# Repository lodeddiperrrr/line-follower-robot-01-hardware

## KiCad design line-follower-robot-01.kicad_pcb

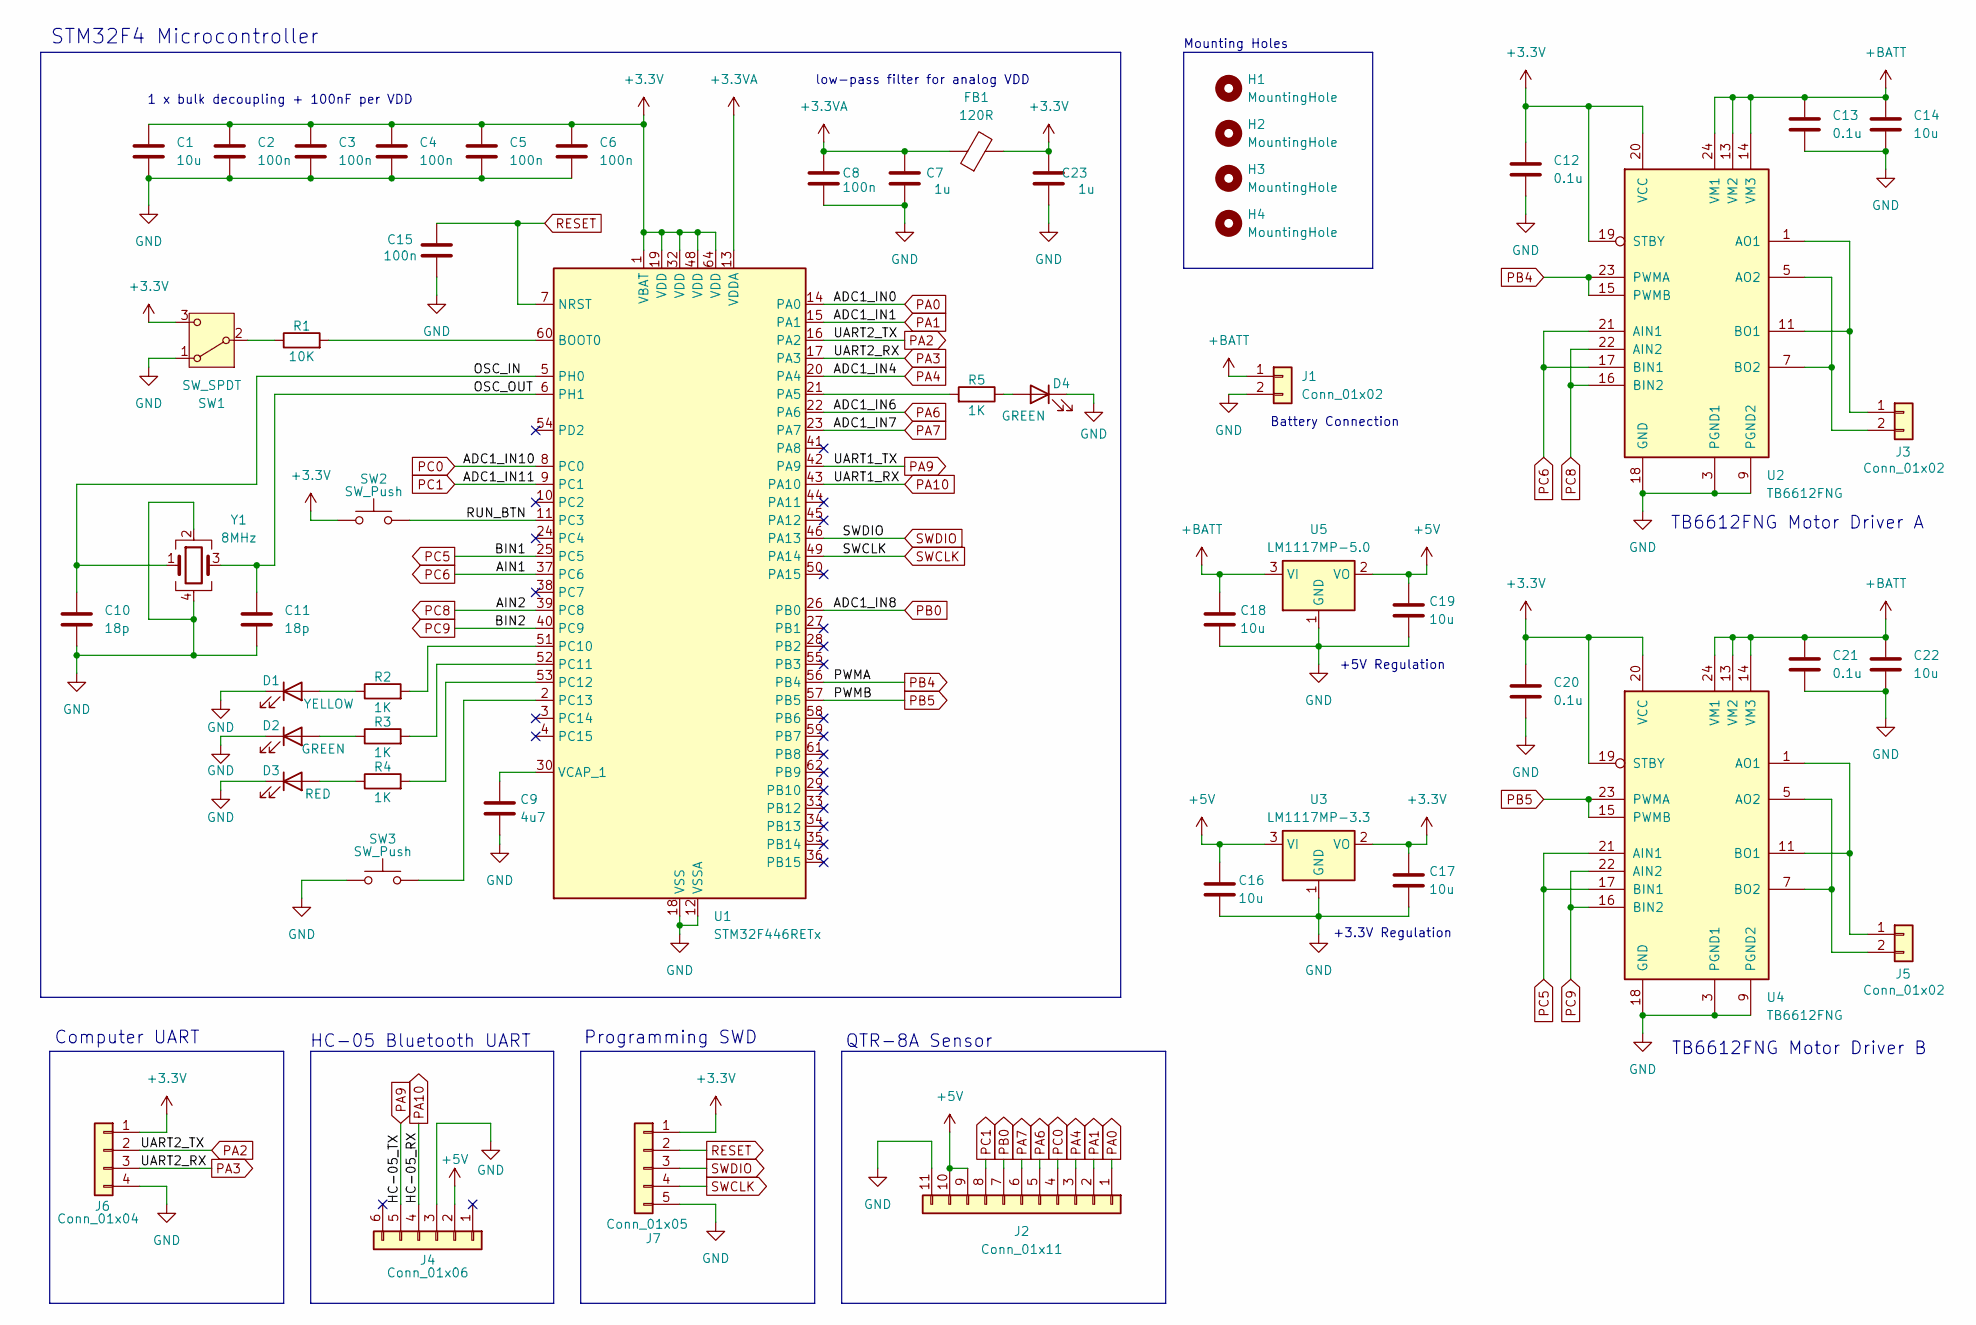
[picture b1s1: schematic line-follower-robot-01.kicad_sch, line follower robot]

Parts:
C1, C14, C16, C17, C18, C19, C22: 10u; C_0603_1608Metric_Pad1.08x0.95mm_HandSolder; LCSC Part # C19702
C2, C3, C4, C5, C6, C8, C15: 100n; C_0603_1608Metric_Pad1.08x0.95mm_HandSolder; LCSC Part # C14663
C7, C23: 1u; C_0603_1608Metric_Pad1.08x0.95mm_HandSolder; LCSC Part # C19702
C9: 4u7; C_0603_1608Metric_Pad1.08x0.95mm_HandSolder; LCSC Part # C19666
C10, C11: 18p; C_0603_1608Metric_Pad1.08x0.95mm_HandSolder; LCSC Part # C1647
C12, C13, C20, C21: 0.1u; C_0603_1608Metric_Pad1.08x0.95mm_HandSolder; LCSC Part # C14663
D1: YELLOW; LED_0603_1608Metric_Pad1.05x0.95mm_HandSolder; LCSC Part # C2287
D2, D4: GREEN; LED_0603_1608Metric_Pad1.05x0.95mm_HandSolder; LCSC Part # C12624
D3: RED; LED_0603_1608Metric_Pad1.05x0.95mm_HandSolder; LCSC Part # C2286
FB1: 120R; L_0603_1608Metric_Pad1.05x0.95mm_HandSolder; LCSC Part # C12391
H1, H2, H3, H4: MountingHole; MountingHole_2.2mm_M2
J1: Conn_01x02; JST_XH_B2B-XH-A_1x02_P2.50mm_Vertical
J2: Conn_01x11; PinHeader_1x11_P2.54mm_Horizontal; LCSC Part # C725903
J3, J5: Conn_01x02; TerminalBlock_Phoenix_MKDS-1,5-2_1x02_P5.00mm_Horizontal
J4: Conn_01x06; PinHeader_1x06_P2.54mm_Vertical
J6: Conn_01x04; PinHeader_1x04_P2.54mm_Vertical
J7: Conn_01x05; PinHeader_1x05_P2.54mm_Vertical
R1: 10K; R_0603_1608Metric_Pad0.98x0.95mm_HandSolder; LCSC Part # C177337
R2, R3, R4, R5: 1K; R_0603_1608Metric_Pad0.98x0.95mm_HandSolder; LCSC Part # C177343
SW1: SW_SPDT; SW_SPDT_CK_JS102011SAQN; LCSC Part # C221660
SW2, SW3: SW_Push; SW_Push_1P1T_NO_CK_KSC7xxJ; LCSC Part # C2799444
U1: STM32F446RETx; LQFP-64_10x10mm_P0.5mm; LCSC Part # C69336
U2, U4: TB6612FNG; SSOP-24_5.3x8.2mm_P0.65mm; LCSC Part # C141517
U3: LM1117MP-3.3; SOT-223-3_TabPin2; LCSC Part # C3750685
U5: LM1117MP-5.0; SOT-223-3_TabPin2; LCSC Part # C498151
Y1: 8MHz; Crystal_SMD_3225-4Pin_3.2x2.5mm; LCSC Part # C57131

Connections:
+3.3V: C1.1, C2.1, C3.1, C4.1, C5.1, C6.1, C12.1, C17.1, C20.1, C23.1, FB1.2, J6.1, J7.1, SW1.3 (C), SW2.1, U1.1 (VBAT), U1.19 (VDD), U1.32 (VDD), U1.48 (VDD), U1.64 (VDD), U2.19 (STBY), U2.20 (VCC), U3.2 (VO), U4.19 (STBY), U4.20 (VCC)
+3.3VA: C7.1, C8.1, FB1.1, U1.13 (VDDA)
+5V: C16.1, C19.1, J2.9, J2.10, J4.2, U3.3 (VI), U5.2 (VO)
+BATT: C13.1, C14.1, C18.1, C21.1, C22.1, J1.1, U2.13 (VM2), U2.14 (VM3), U2.24 (VM1), U4.13 (VM2), U4.14 (VM3), U4.24 (VM1), U5.3 (VI)
/OSC_IN: C10.1, U1.5 (PH0), Y1.1
/OSC_OUT: C11.1, U1.6 (PH1), Y1.3
/RUN_BTN: SW2.2, U1.11 (PC3)
GND: C1.2, C2.2, C3.2, C4.2, C5.2, C6.2, C7.2, C8.2, C9.2, C10.2, C11.2, C12.2, C13.2, C14.2, C15.2, C16.2, C17.2, C18.2, C19.2, C20.2, C21.2, C22.2, C23.2, D1.1 (K), D2.1 (K), D3.1 (K), D4.1 (K), J1.2, J2.11, J4.3, J6.4, J7.5, SW1.1 (A), SW3.1, U1.12 (VSSA), U1.18 (VSS), U1.31 (VSS), U1.47 (VSS), U1.63 (VSS), U2.3 (PGND1), U2.4 (PGND1), U2.9 (PGND2), U2.10 (PGND2), U2.18 (GND), U3.1 (GND), U4.3 (PGND1), U4.4 (PGND1), U4.9 (PGND2), U4.10 (PGND2), U4.18 (GND), U5.1 (GND), Y1.2, Y1.4
unnamed: D1.2 (A), R2.1
unnamed: D2.2 (A), R3.1
unnamed: D3.2 (A), R4.1
unnamed: D4.2 (A), R5.1
unnamed: J3.1, U2.1 (AO1), U2.2 (AO1), U2.11 (BO1), U2.12 (BO1)
unnamed: J3.2, U2.5 (AO2), U2.6 (AO2), U2.7 (BO2), U2.8 (BO2)
unnamed: J5.1, U4.1 (AO1), U4.2 (AO1), U4.11 (BO1), U4.12 (BO1)
unnamed: J5.2, U4.5 (AO2), U4.6 (AO2), U4.7 (BO2), U4.8 (BO2)
unnamed: R1.1, SW1.2 (B)
unnamed: R1.2, U1.60 (BOOT0)
unnamed: R5.2, U1.21 (PA5)
unnamed: R2.2, U1.51 (PC10)
unnamed: R3.2, U1.52 (PC11)
unnamed: R4.2, U1.53 (PC12)
unnamed: SW3.2, U1.2 (PC13)
unnamed: C9.1, U1.30 (VCAP_1)
PA0: J2.1, U1.14 (PA0)
PA1: J2.2, U1.15 (PA1)
PA2: J6.2, U1.16 (PA2)
PA3: J6.3, U1.17 (PA3)
PA4: J2.3, U1.20 (PA4)
PA6: J2.5, U1.22 (PA6)
PA7: J2.6, U1.23 (PA7)
PA9: J4.5, U1.42 (PA9)
PA10: J4.4, U1.43 (PA10)
PB0: J2.7, U1.26 (PB0)
PB4: U1.56 (PB4), U2.15 (PWMB), U2.23 (PWMA)
PB5: U1.57 (PB5), U4.15 (PWMB), U4.23 (PWMA)
PC0: J2.4, U1.8 (PC0)
PC1: J2.8, U1.9 (PC1)
PC5: U1.25 (PC5), U4.17 (BIN1), U4.21 (AIN1)
PC6: U1.37 (PC6), U2.17 (BIN1), U2.21 (AIN1)
PC8: U1.39 (PC8), U2.16 (BIN2), U2.22 (AIN2)
PC9: U1.40 (PC9), U4.16 (BIN2), U4.22 (AIN2)
RESET: C15.1, J7.2, U1.7 (NRST)
SWCLK: J7.4, U1.49 (PA14)
SWDIO: J7.3, U1.46 (PA13)

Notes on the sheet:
Computer UART
Battery Connection
1 x bulk decoupling + 100nF per VDD
+5V Regulation
STM32F4 Microcontroller
TB6612FNG Motor Driver A
TB6612FNG Motor Driver B
HC-05 Bluetooth UART
QTR-8A Sensor
+3.3V Regulation
low-pass filter for analog VDD
Mounting Holes
Programming SWD

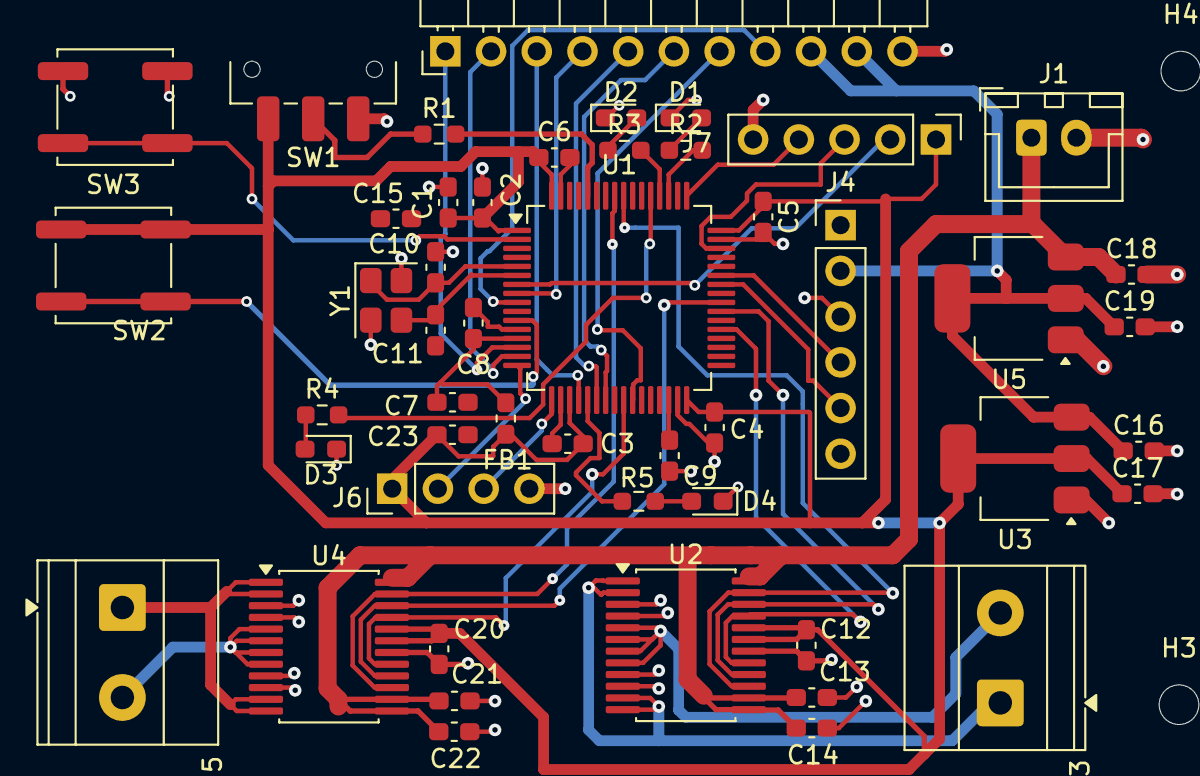
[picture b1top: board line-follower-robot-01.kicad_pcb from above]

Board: 2 copper layers, 53 parts (0 on the bottom side), 45 nets.
